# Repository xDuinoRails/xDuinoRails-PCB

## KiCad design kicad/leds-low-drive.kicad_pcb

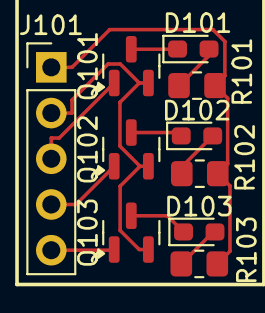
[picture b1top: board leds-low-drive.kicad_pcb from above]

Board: 2 copper layers, 10 parts (0 on the bottom side), 11 nets.

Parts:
D101, D102, D103: LED_RED; LED_0603_1608Metric_Pad1.05x0.95mm_HandSolder
J101: Conn_01x05; PinHeader_1x05_P2.54mm_Vertical
Q101, Q102, Q103: S8050; 8x50_SOT-23
R101, R102, R103: 1k; R_0805_2012Metric_Pad1.20x1.40mm_HandSolder

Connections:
/+3v3: J101.1, R101.1, R102.1, R103.1
/GND: J101.2, Q101.1 (E), Q102.1 (E), Q103.1 (E)
/LED1: J101.3, Q101.2 (B)
/LED2: J101.4, Q102.2 (B)
/LED3: J101.5, Q103.2 (B)
unnamed: D101.2 (A), R101.2
unnamed: D101.1 (K), Q101.3 (C)
unnamed: D102.2 (A), R102.2
unnamed: D102.1 (K), Q102.3 (C)
unnamed: D103.2 (A), R103.2
unnamed: D103.1 (K), Q103.3 (C)

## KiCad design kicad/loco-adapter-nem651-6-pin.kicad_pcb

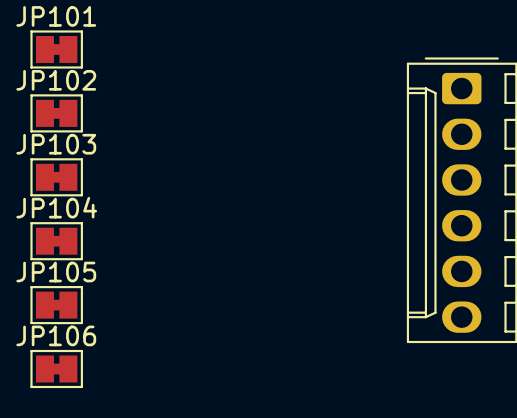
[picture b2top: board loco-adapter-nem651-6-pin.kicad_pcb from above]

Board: 2 copper layers, 7 parts (0 on the bottom side), 6 nets, no tracks yet.

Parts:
J104: Conn_01x06; Molex_KK-254_AE-6410-06A_1x06_P2.54mm_Vertical
JP101, JP102, JP103, JP104, JP105, JP106: SolderJumper_2_Bridged; SolderJumper-2_P1.3mm_Bridged_Pad1.0x1.5mm

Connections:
/AMP_MOTOR0: J104.2, JP101.2 (B)
/AMP_MOTOR1: J104.1, JP102.2 (B)
/DCC0: J104.4, JP103.2 (B)
/DCC1: J104.3, JP104.2 (B)
/FUNC0: J104.6, JP106.2 (B)
/FUNC1: J104.5, JP105.2 (B)

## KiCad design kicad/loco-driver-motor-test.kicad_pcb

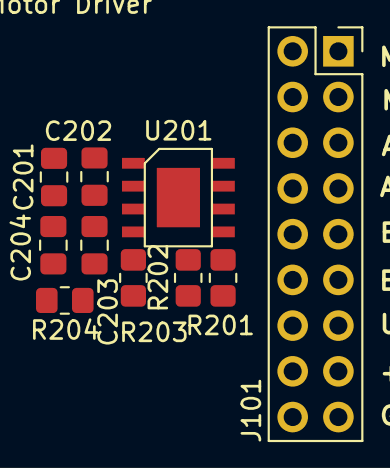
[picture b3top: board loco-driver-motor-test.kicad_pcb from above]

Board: 2 copper layers, 10 parts (0 on the bottom side), 9 nets, no tracks yet.

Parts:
C201, C203: 10uF; C_0805_2012Metric_Pad1.18x1.45mm_HandSolder
C202, C204: 100nF; C_0805_2012Metric_Pad1.18x1.45mm_HandSolder
J101: Conn_02x09_Odd_Even; PinSocket_2x09_P2.54mm_Vertical
R201, R203: 6k8; R_0805_2012Metric_Pad1.20x1.40mm_HandSolder
R202, R204: 1k; R_0805_2012Metric_Pad1.20x1.40mm_HandSolder
U201: BDR6133

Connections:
/J_+3v3: C201.1, C202.1, J101.15, U201.2 (VCC)
/J_AMP_MOTOR0: J101.5, R203.2, U201.4 (OUTA)
/J_AMP_MOTOR1: J101.7, R201.2, U201.5 (OUTB)
/J_EMF_MOTOR0: J101.9, R203.1, R204.1
/J_EMF_MOTOR1: J101.11, R201.1, R202.1
/J_MOTOR0: J101.1, U201.6 (INA)
/J_MOTOR1: J101.3, U201.7 (INB)
/J_U+: C203.1, C204.1, J101.13, U201.3 (VM)
PGND: C201.2, C202.2, C203.2, C204.2, J101.17, R202.2, R204.2, U201.1 (GND), U201.9 (PGND)

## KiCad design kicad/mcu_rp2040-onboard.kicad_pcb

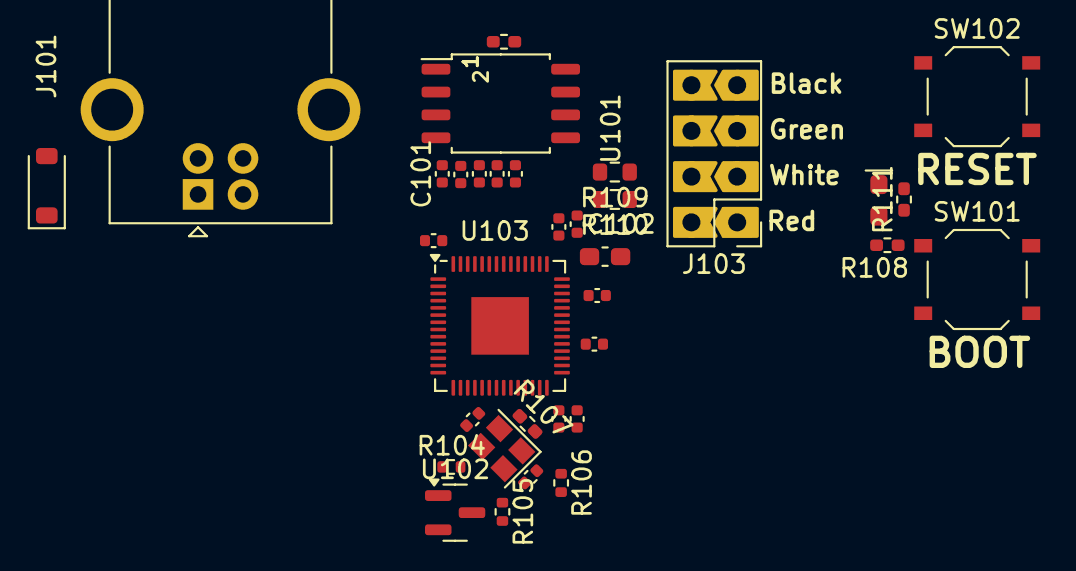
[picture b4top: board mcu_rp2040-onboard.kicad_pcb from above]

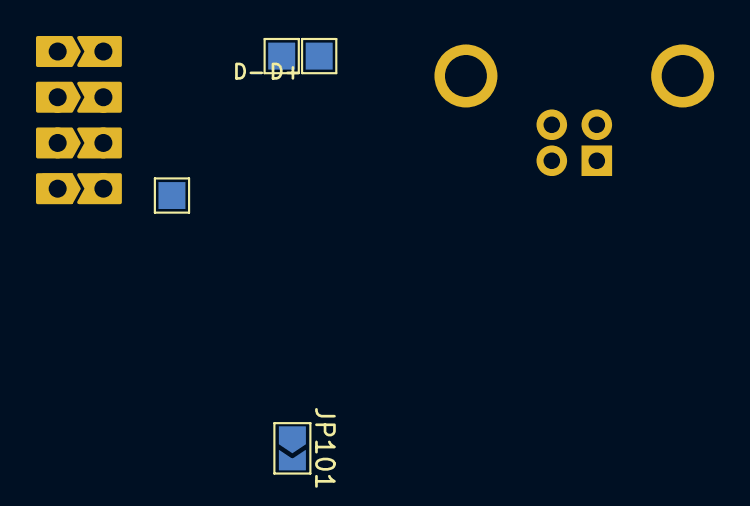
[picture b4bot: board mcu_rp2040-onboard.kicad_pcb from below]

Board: 2 copper layers, 38 parts (4 on the bottom side), 24 nets, no tracks yet.

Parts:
C101, C105, C106, C108, C110, C111, C112, C113, C114, C115: 100n; C_0402_1005Metric
C102: 10n C0G; C_0603_1608Metric_Pad1.08x0.95mm_HandSolder
C103, C104: 18p; C_0402_1005Metric
C107, C109: 1u; C_0402_1005Metric
D101: B5819W; D_SOD-123
D102: LED; LED_0603_1608Metric_Pad1.05x0.95mm_HandSolder
J101: USB_B; USB_B_OST_USB-B1HSxx_Horizontal
J103: Conn_02x04_Odd_Even; PinHeaderJP_2x04_P2.54mm_Vertical
JP101: VREF; SolderJumper-2_P1.3mm_Open_TrianglePad1.0x1.5mm
R101: DNP; R_0402_1005Metric_Pad0.72x0.64mm_HandSolder
R104: 680R; R_0402_1005Metric
R105: 3k3; R_0402_1005Metric
R106: 150R; R_0402_1005Metric
R107, R108, R111: 1k; R_0402_1005Metric_Pad0.72x0.64mm_HandSolder
R109, R110: 27R; R_0603_1608Metric
SW101: BOOTSEL; SW_Push_1P1T_XKB_TS-1187A
SW102: RESET; SW_Push_1P1T_XKB_TS-1187A
TP101: VREG; TestPoint_Pad_1.5x1.5mm
TP102: D+; TestPoint_Pad_1.5x1.5mm
TP103: D-; TestPoint_Pad_1.5x1.5mm
U101: W25Q128JVSIQ; SOIC-8_5.23x5.23mm_P1.27mm
U102: TL431DBZ; SOT-23
U103: RP2040; QFN-56-1EP_7x7mm_P0.4mm_EP3.2x3.2mm
Y101: ECS-120-12-36-AGN-TR3; Crystal_SMD_2520-4Pin_2.5x2.0mm

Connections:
+1V1: C105.1, C106.1, C107.1, TP101.1, U103.23 (DVDD), U103.45 (VREG_VOUT), U103.50 (DVDD)
/2v5_VREF: R104.1, R105.2, U102.2 (REF)
/3V0_VREF: JP101.2 (B), R104.2, R106.1, U102.1 (K)
/+3V3: C101.1, C108.1, C109.1, C110.1, C111.1, C112.1, C113.1, C114.1, C115.1, R101.1, R106.2, U101.8 (VCC), U103.1 (IOVDD), U103.10 (IOVDD), U103.22 (IOVDD), U103.33 (IOVDD), U103.42 (IOVDD), U103.44 (VREG_IN), U103.48 (USB_VDD), U103.49 (IOVDD)
/ADC_VREF: C102.1, JP101.1 (A), U103.43 (ADC_AVDD)
/D+: J103.5, J103.6, R109.1, TP102.1
/D-: J101.2 (D-), J103.3, J103.4, R110.1, TP103.1
/DN: R110.2, U103.46 (USB_DM)
/DP: R109.2, U103.47 (USB_DP)
/GND: C101.2, C102.2, C103.2, C104.2, C105.2, C106.2, C107.2, C108.2, C109.2, C110.2, C111.2, C112.2, C113.2, C114.2, C115.2, J101.4 (GND), J101.5 (Shield), J103.7, J103.8, R105.1, R111.2, SW101.2, SW102.2, U101.4 (GND), U102.3 (A), U103.19 (TESTEN), U103.57 (GND), Y101.2, Y101.4
/GPIO23: D102.2 (A), U103.35 (GPIO23)
/QSPI_SCLK: U101.6 (CLK), U103.52 (QSPI_SCLK)
/QSPI_SD0: U101.5 (DI(IO0)), U103.53 (QSPI_SD0)
/QSPI_SD1: U101.2 (DO(IO1)), U103.55 (QSPI_SD1)
/QSPI_SD2: U101.3 (IO2), U103.54 (QSPI_SD2)
/QSPI_SD3: U101.7 (IO3), U103.51 (QSPI_SD3)
/QSPI_SS: R101.2, R108.1, U101.1 (~CS), U103.56 (QSPI_SS)
/RESET_RUN: SW102.1, U103.26 (RUN)
/XIN: C103.1, U103.20 (XIN), Y101.3
/XOUT: R107.1, U103.21 (XOUT)
unnamed: C104.1, R107.2, Y101.1
unnamed: D102.1 (K), R111.1
unnamed: R108.2, SW101.1
VBUS: D101.2 (A), J101.1 (VBUS), J103.1, J103.2

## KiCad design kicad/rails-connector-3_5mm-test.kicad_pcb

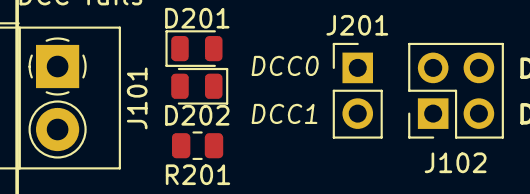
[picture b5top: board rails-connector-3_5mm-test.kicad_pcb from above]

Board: 2 copper layers, 6 parts (0 on the bottom side), 3 nets, no tracks yet.

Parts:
D201: LED_YELLOW; LED_0805_2012Metric
D202: LED_WHITE; LED_0805_2012Metric
J101: Conn_01x02; TerminalBlock_4Ucon_1x02_P3.50mm_Horizontal
J102: Conn_02x02_Odd_Even; PinSocket_2x02_P2.54mm_Vertical
J201: Conn_01x02; PinHeader_1x02_P2.54mm_Vertical
R201: 10k; R_0805_2012Metric

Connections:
/J_DCC0: J101.2, J102.1, J201.2, R201.1
/J_DCC1: D201.2 (A), D202.1 (K), J101.1, J102.3, J201.1
unnamed: D201.1 (K), D202.2 (A), R201.2

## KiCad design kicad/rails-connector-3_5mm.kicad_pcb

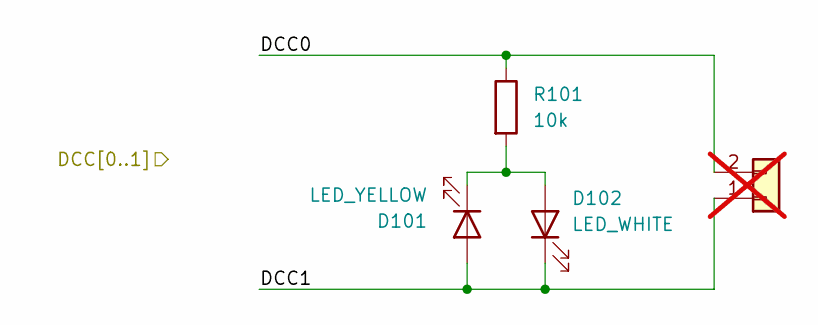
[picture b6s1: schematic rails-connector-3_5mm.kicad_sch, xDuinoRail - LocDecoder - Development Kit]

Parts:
D101: LED_YELLOW; LED_0805_2012Metric
D102: LED_WHITE; LED_0805_2012Metric
J101: Conn_01x02; PinSocket_1x02_P2.54mm_Vertical; not fitted
R101: 10k; R_0805_2012Metric_Pad1.20x1.40mm_HandSolder

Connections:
/DCC0: J101.2, R101.1
/DCC1: D101.2 (A), D102.1 (K), J101.1
unnamed: D101.1 (K), D102.2 (A), R101.2

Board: 2 copper layers, 4 parts (0 on the bottom side), 3 nets, no tracks yet.
